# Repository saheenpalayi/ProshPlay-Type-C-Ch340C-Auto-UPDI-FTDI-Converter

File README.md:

# ProshPlay-Type-C-Ch340C-Auto-UPDI-FTDI-Converter

## Schematic

## PCB Layout

## 3D PCB

## Reference  
- [Arduino Forum Yet another UPDI ro rammer Mk II](https://forum.arduino.cc/t/yet-another-updi-programmer-mk-ii/1357056/2)

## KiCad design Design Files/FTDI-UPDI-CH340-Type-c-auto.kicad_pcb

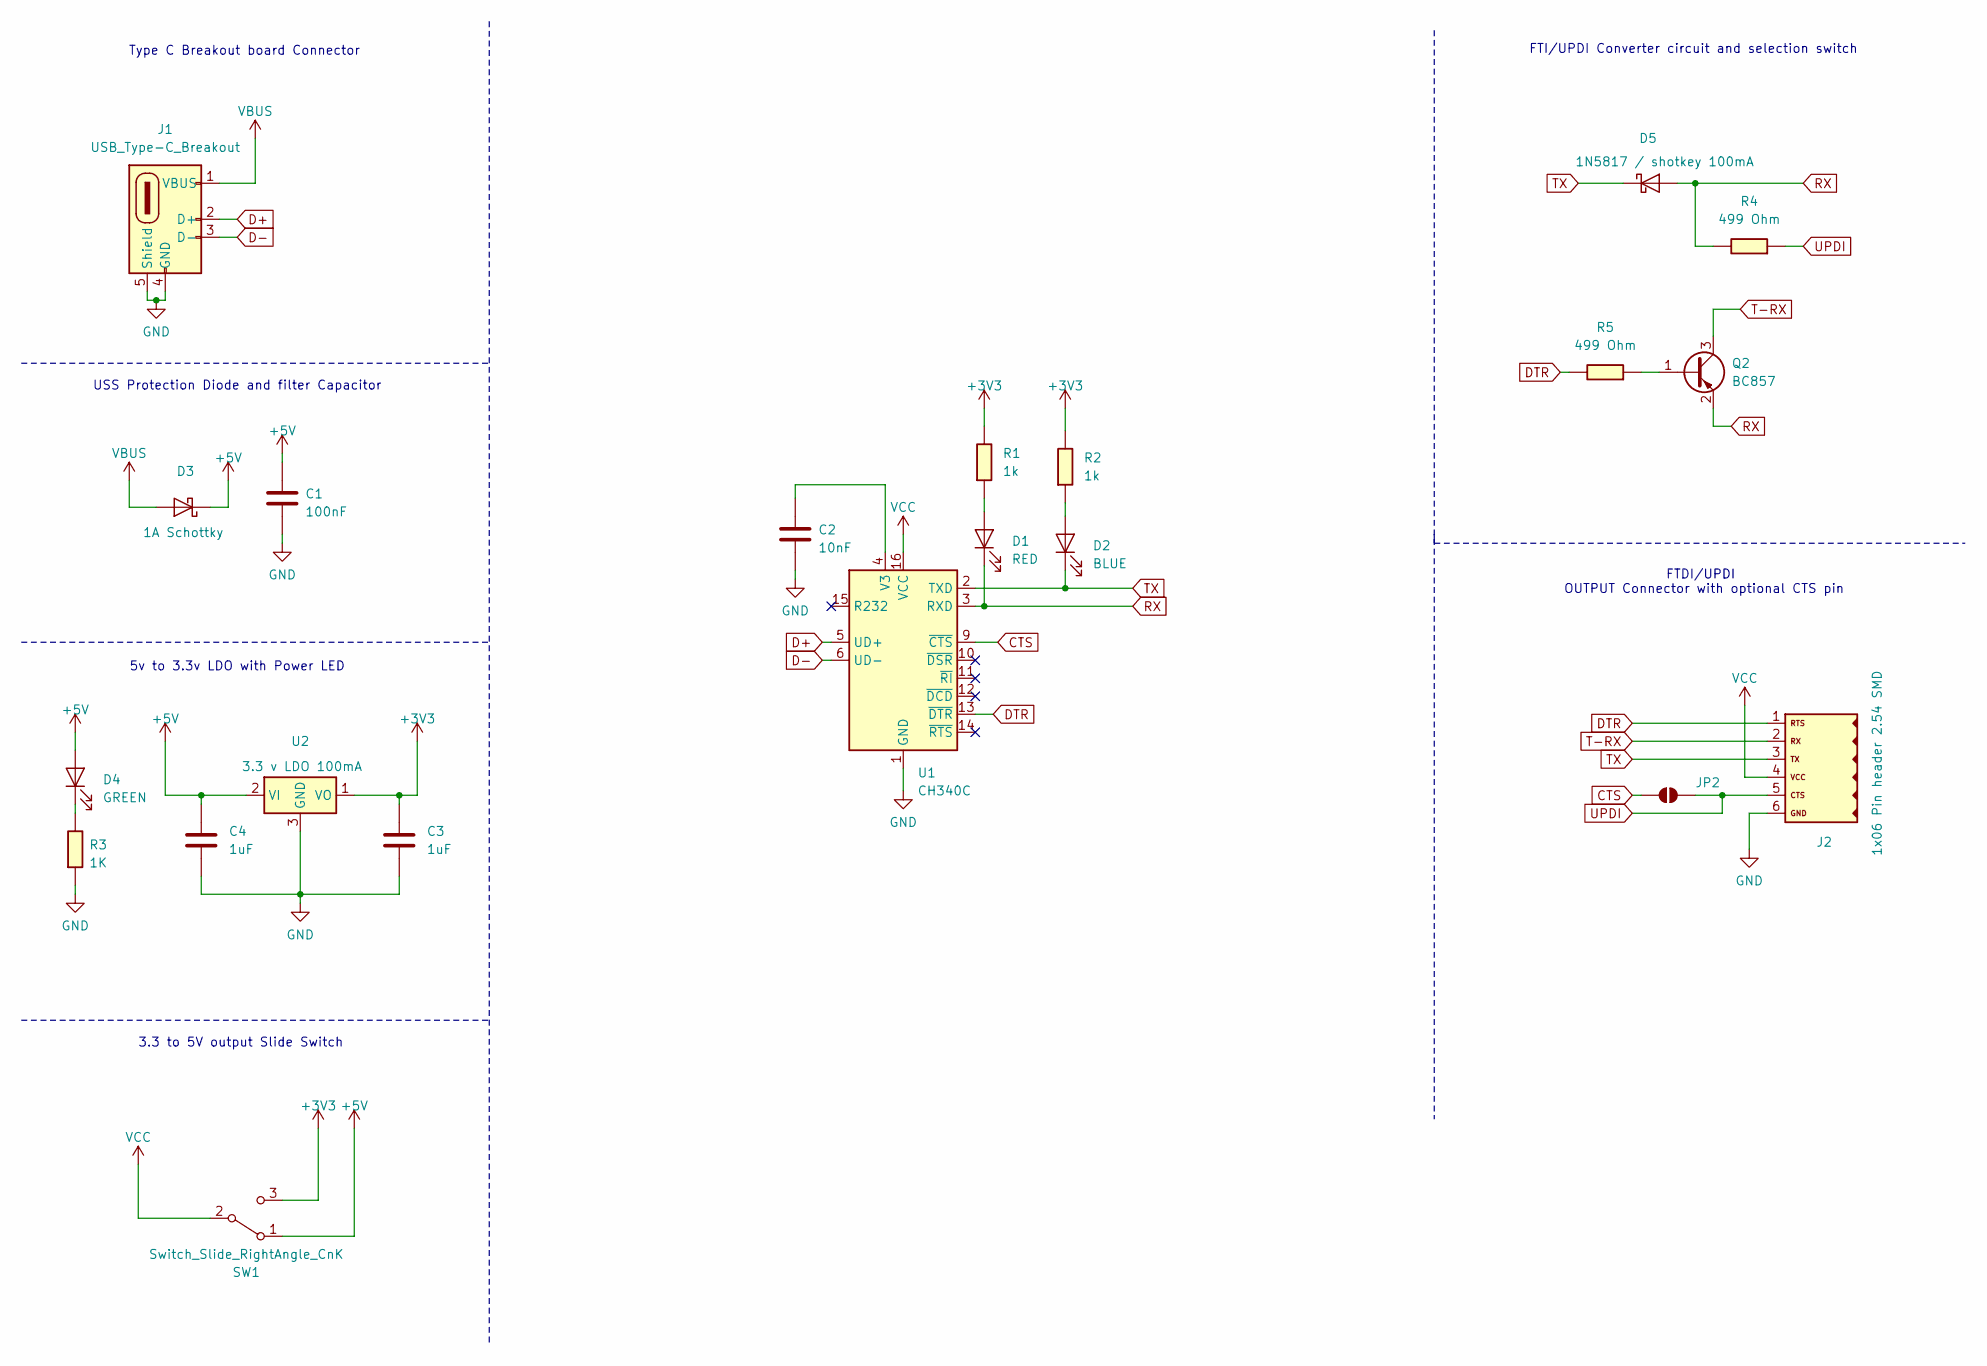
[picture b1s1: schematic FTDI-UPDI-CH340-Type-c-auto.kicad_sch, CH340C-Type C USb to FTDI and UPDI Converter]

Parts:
C1: 100nF; C_1206
C2: 10nF; C_1206
C3, C4: 1uF; C_1206
D1: RED; LED_1206
D2: BLUE; LED_1206
D3: 1A Schottky; SOD-123T
D4: GREEN; LED_1206
D5: 1N5817 / shotkey 100mA; Diode_Schottky_MiniSMA
J1: USB_Type-C_Breakout; ProshPlay-Type-C-breakout-board
J2: 1x06 Pin header 2.54 SMD; PinSocket_1x06_P2.54mm_Horizontal_SMD
JP2: SolderJumper_2_Open; SolderJumper-2_P1.3mm_Open_RoundedPad1.0x1.5mm
Q2: BC857; SOT-23
R1, R2: 1k; R_1206
R3: 1K; R_1206
R4, R5: 499 Ohm; R_1206
SW1: Switch_Slide_RightAngle_CnK; Switch_Slide_RightAngle_CnK_AYZ0102AGRLC_7.2x3mm
U1: CH340C; SOIC-16_3.9x9.9mm_P1.27mm
U2: 3.3 v LDO 100mA; SOT-23-3

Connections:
+3V3: C3.1, R1.1, R2.1, SW1.3 (C), U2.1 (VO)
+5V: C1.1, C4.1, D3.1 (K), D4.2 (A), SW1.1 (A), U2.2 (VI)
CTS: JP2.1 (A), U1.9 (~CTS)
D+: J1.2 (D+), U1.5 (UD+)
D-: J1.3 (D-), U1.6 (UD-)
DTR: J2.1, R5.1, U1.13 (~DTR)
GND: C1.2, C2.2, C3.2, C4.2, J1.4 (GND), J1.5 (Shield), J2.6, R3.2, U1.1 (GND), U2.3 (GND)
unnamed: D1.2 (A), R1.2
unnamed: D2.2 (A), R2.2
unnamed: D4.1 (K), R3.1
unnamed: Q2.1 (B), R5.2
unnamed: C2.1, U1.4 (V3)
RX: D1.1 (K), D5.2 (A), Q2.2 (E), R4.1, U1.3 (RXD)
T-RX: J2.2, Q2.3 (C)
TX: D2.1 (K), D5.1 (K), J2.3, U1.2 (TXD)
UPDI: J2.5, JP2.2 (B), R4.2
VBUS: D3.2 (A), J1.1 (VBUS)
VCC: J2.4, SW1.2 (B), U1.16 (VCC)

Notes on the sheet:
USS Protection Diode and filter Capacitor
5v to 3.3v LDO with Power LED
FTI/UPDI Converter circuit and selection switch
FTDI/UPDI OUTPUT Connector with optional CTS pin
Type C Breakout board Connector
3.3 to 5V output Slide Switch

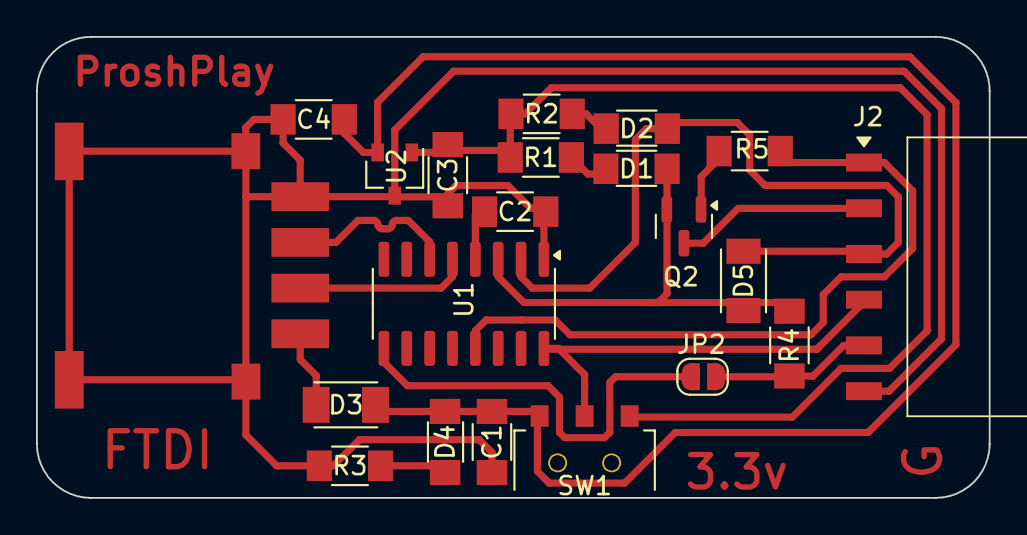
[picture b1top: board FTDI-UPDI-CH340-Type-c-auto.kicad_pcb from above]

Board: 2 copper layers, 52.9 x 25.6 mm, 21 parts (0 on the bottom side), 18 nets.

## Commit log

2025-05-14 added files and images
2025-05-14 updated the readme
